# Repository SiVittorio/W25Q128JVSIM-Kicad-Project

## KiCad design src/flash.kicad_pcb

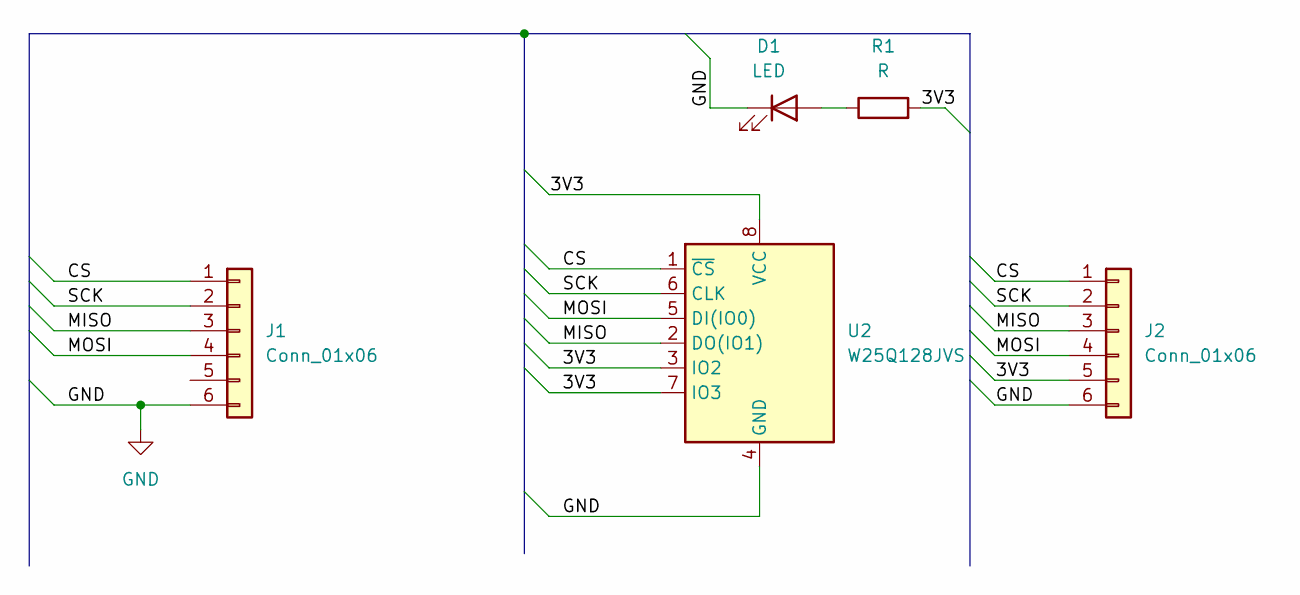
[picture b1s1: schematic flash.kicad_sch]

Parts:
D1: LED; LED_D5.0mm
J1, J2: Conn_01x06; PinHeader_1x06_P2.54mm_Vertical
R1: R; R_Axial_DIN0411_L9.9mm_D3.6mm_P25.40mm_Horizontal
U2: W25Q128JVS; SOIC-8_5.23x5.23mm_P1.27mm

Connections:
/3V3: J2.5, R1.2, U2.3 (IO2), U2.7 (IO3), U2.8 (VCC)
/CS: J1.1, J2.1, U2.1 (~CS)
/MISO: J1.3, J2.3, U2.2 (DO(IO1))
/MOSI: J1.4, J2.4, U2.5 (DI(IO0))
/SCK: J1.2, J2.2, U2.6 (CLK)
GND: D1.1 (K), J1.6, J2.6, U2.4 (GND)
unnamed: D1.2 (A), R1.1

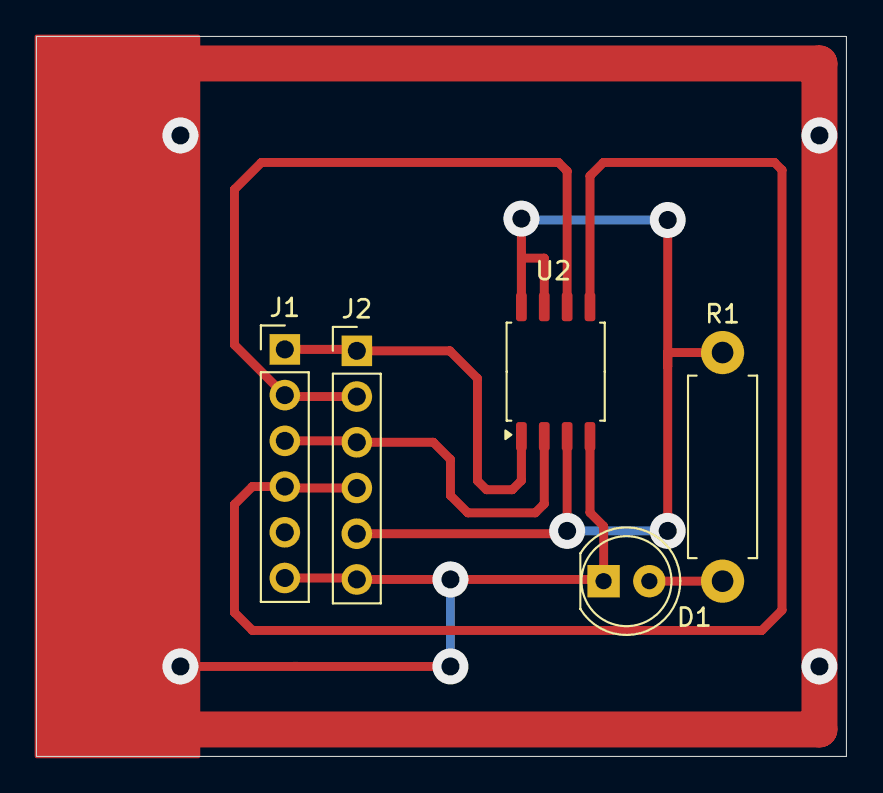
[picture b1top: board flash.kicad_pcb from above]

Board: 2 copper layers, 45.0 x 40.0 mm, 5 parts (0 on the bottom side), 7 nets.

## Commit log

2025-03-08 feat: add board scheme
2025-03-10 fix: remove GND fill, edit flash routes
2025-03-13 feat: bigger size
    Bigger size for comfortable production
2025-03-13 feat: prepare for prod
2025-03-26 fix: more space for dev
2025-03-27 fix: some wires are gone
